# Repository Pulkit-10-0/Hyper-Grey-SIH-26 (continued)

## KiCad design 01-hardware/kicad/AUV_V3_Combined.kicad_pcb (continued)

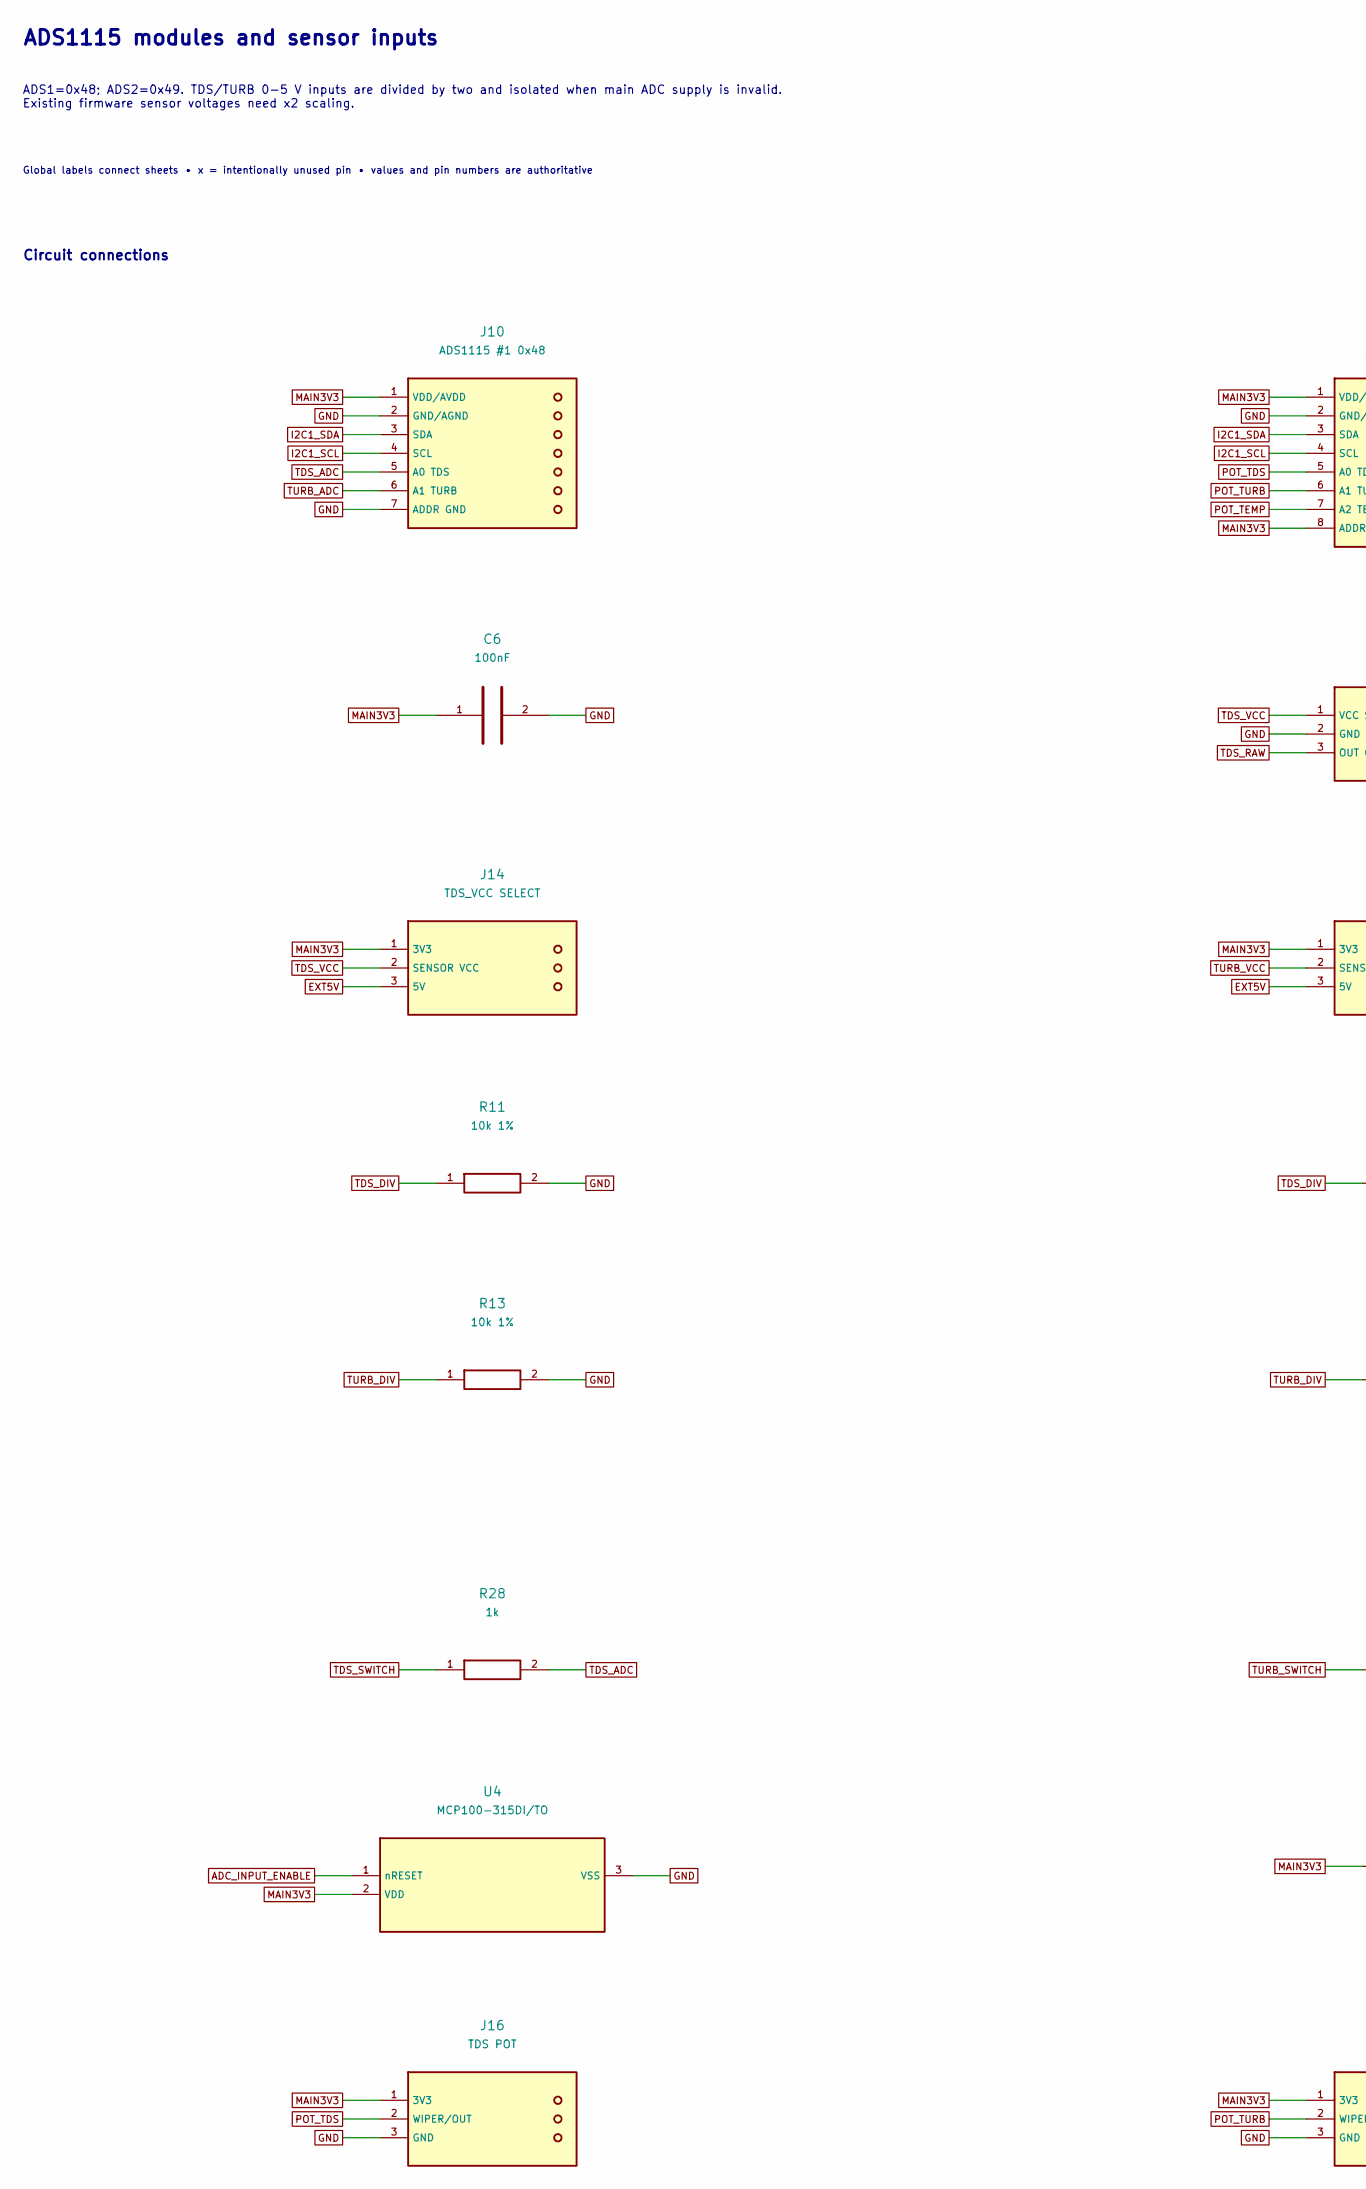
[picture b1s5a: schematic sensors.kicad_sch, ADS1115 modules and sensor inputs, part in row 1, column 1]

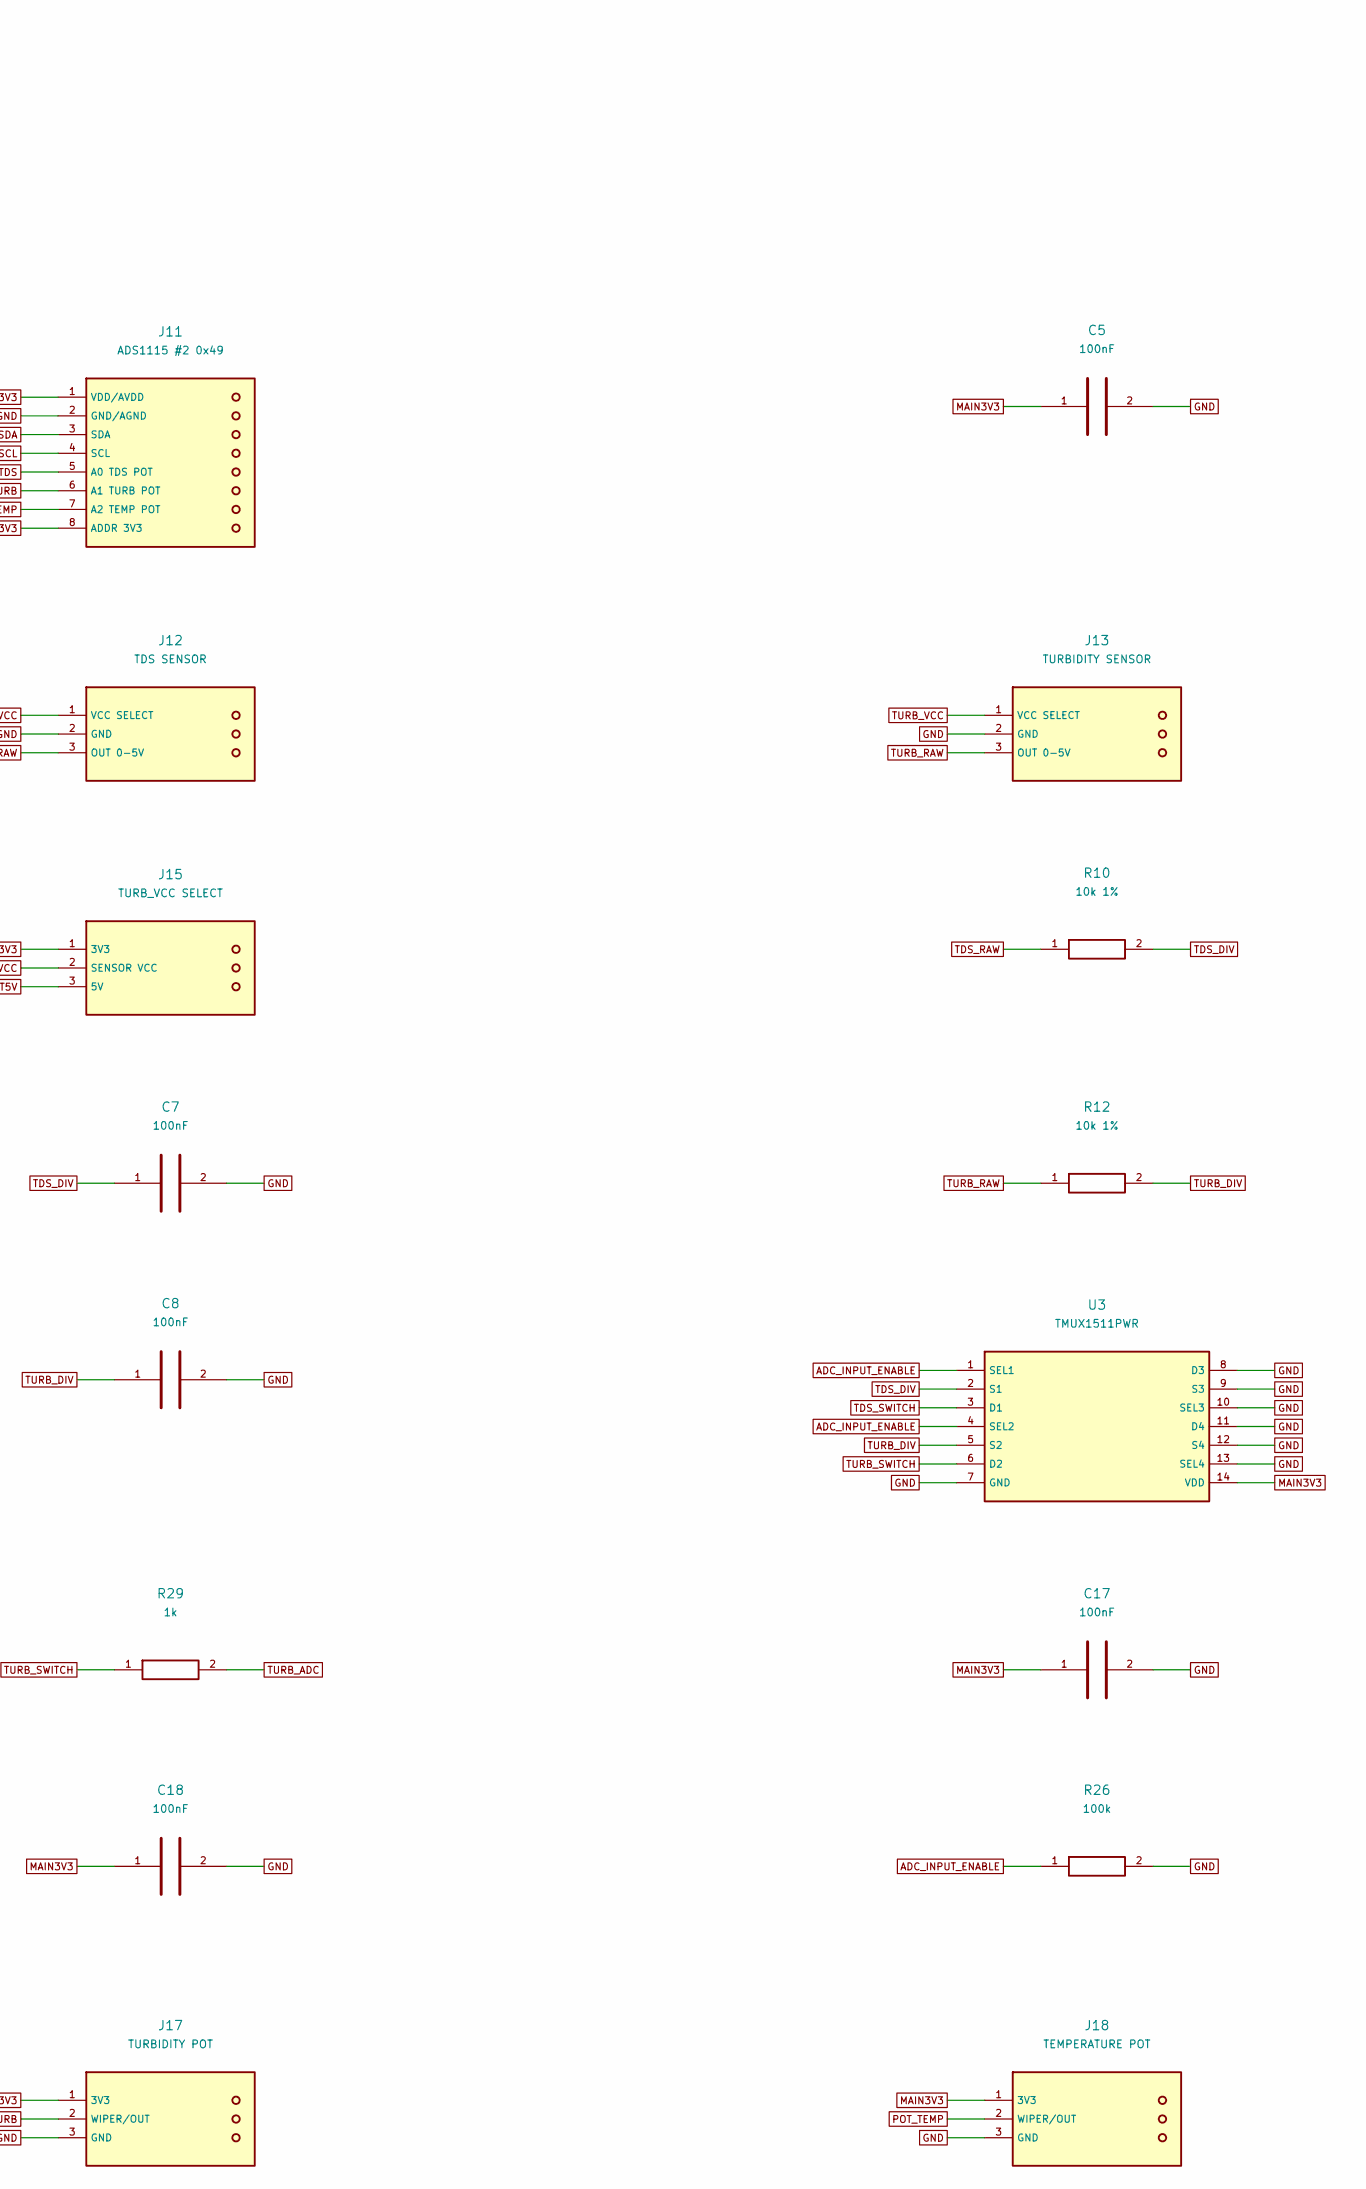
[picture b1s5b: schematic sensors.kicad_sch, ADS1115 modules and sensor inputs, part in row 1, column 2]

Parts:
C5, C6, C7, C8, C17, C18: 100nF; C_Disc_D3.0mm_W1.6mm_P2.50mm
J10: ADS1115 #1 0x48; WirePads_1x07; MPN Bare plated through-hole wiring pads
J11: ADS1115 #2 0x49; WirePads_1x08; MPN Bare plated through-hole wiring pads
J12: TDS SENSOR; WirePads_1x03; MPN Bare plated through-hole wiring pads
J13: TURBIDITY SENSOR; WirePads_1x03; MPN Bare plated through-hole wiring pads
J14: TDS_VCC SELECT; PinHeader_1x03_P2.54mm_Vertical
J15: TURB_VCC SELECT; PinHeader_1x03_P2.54mm_Vertical
J16: TDS POT; WirePads_1x03; MPN Bare plated through-hole wiring pads
J17: TURBIDITY POT; WirePads_1x03; MPN Bare plated through-hole wiring pads
J18: TEMPERATURE POT; WirePads_1x03; MPN Bare plated through-hole wiring pads
R10, R11, R12, R13: 10k 1%; R_Axial_DIN0207_L6.3mm_D2.5mm_P7.62mm_Horizontal
R26: 100k; R_Axial_DIN0207_L6.3mm_D2.5mm_P7.62mm_Horizontal
R28, R29: 1k; R_Axial_DIN0207_L6.3mm_D2.5mm_P7.62mm_Horizontal
U3: TMUX1511PWR; TSSOP-14_4.4x5mm_P0.65mm; MPN TMUX1511PWR
U4: MCP100-315DI/TO; TO-92_Inline_Wide; MPN MCP100-315DI/TO

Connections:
ADC_INPUT_ENABLE: R26.1, U3.1 (SEL1), U3.4 (SEL2), U4.1 (nRESET)
EXT5V: J14.3 (5V), J15.3 (5V); also elsewhere on the board
GND: C5.2, C6.2, C7.2, C8.2, C17.2, C18.2, J10.2 (GND/AGND), J10.7 (ADDR GND), J11.2 (GND/AGND), J12.2 (GND), J13.2 (GND), J16.3 (GND), J17.3 (GND), J18.3 (GND), R11.2, R13.2, R26.2, U3.7 (GND), U3.8 (D3), U3.9 (S3), U3.10 (SEL3), U3.11 (D4), U3.12 (S4), U3.13 (SEL4), U4.3 (VSS); also elsewhere on the board
I2C1_SCL: J10.4 (SCL), J11.4 (SCL); also elsewhere on the board
I2C1_SDA: J10.3 (SDA), J11.3 (SDA); also elsewhere on the board
MAIN3V3: C5.1, C6.1, C17.1, C18.1, J10.1 (VDD/AVDD), J11.1 (VDD/AVDD), J11.8 (ADDR 3V3), J14.1 (3V3), J15.1 (3V3), J16.1 (3V3), J17.1 (3V3), J18.1 (3V3), U3.14 (VDD), U4.2 (VDD); also elsewhere on the board
POT_TDS: J11.5 (A0 TDS POT), J16.2 (WIPER/OUT)
POT_TEMP: J11.7 (A2 TEMP POT), J18.2 (WIPER/OUT)
POT_TURB: J11.6 (A1 TURB POT), J17.2 (WIPER/OUT)
TDS_ADC: J10.5 (A0 TDS), R28.2
TDS_DIV: C7.1, R10.2, R11.1, U3.2 (S1)
TDS_RAW: J12.3 (OUT 0-5V), R10.1
TDS_SWITCH: R28.1, U3.3 (D1)
TDS_VCC: J12.1 (VCC SELECT), J14.2 (SENSOR VCC)
TURB_ADC: J10.6 (A1 TURB), R29.2
TURB_DIV: C8.1, R12.2, R13.1, U3.5 (S2)
TURB_RAW: J13.3 (OUT 0-5V), R12.1
TURB_SWITCH: R29.1, U3.6 (D2)
TURB_VCC: J13.1 (VCC SELECT), J15.2 (SENSOR VCC)

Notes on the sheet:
ADS1115 modules and sensor inputs
ADS1=0x48; ADS2=0x49. TDS/TURB 0-5 V inputs are divided by two and isolated when main ADC supply is invalid. Existing firmware sensor voltages need x2 scaling.
Global labels connect sheets • x = intentionally unused pin • values and pin numbers are authoritative
Circuit connections

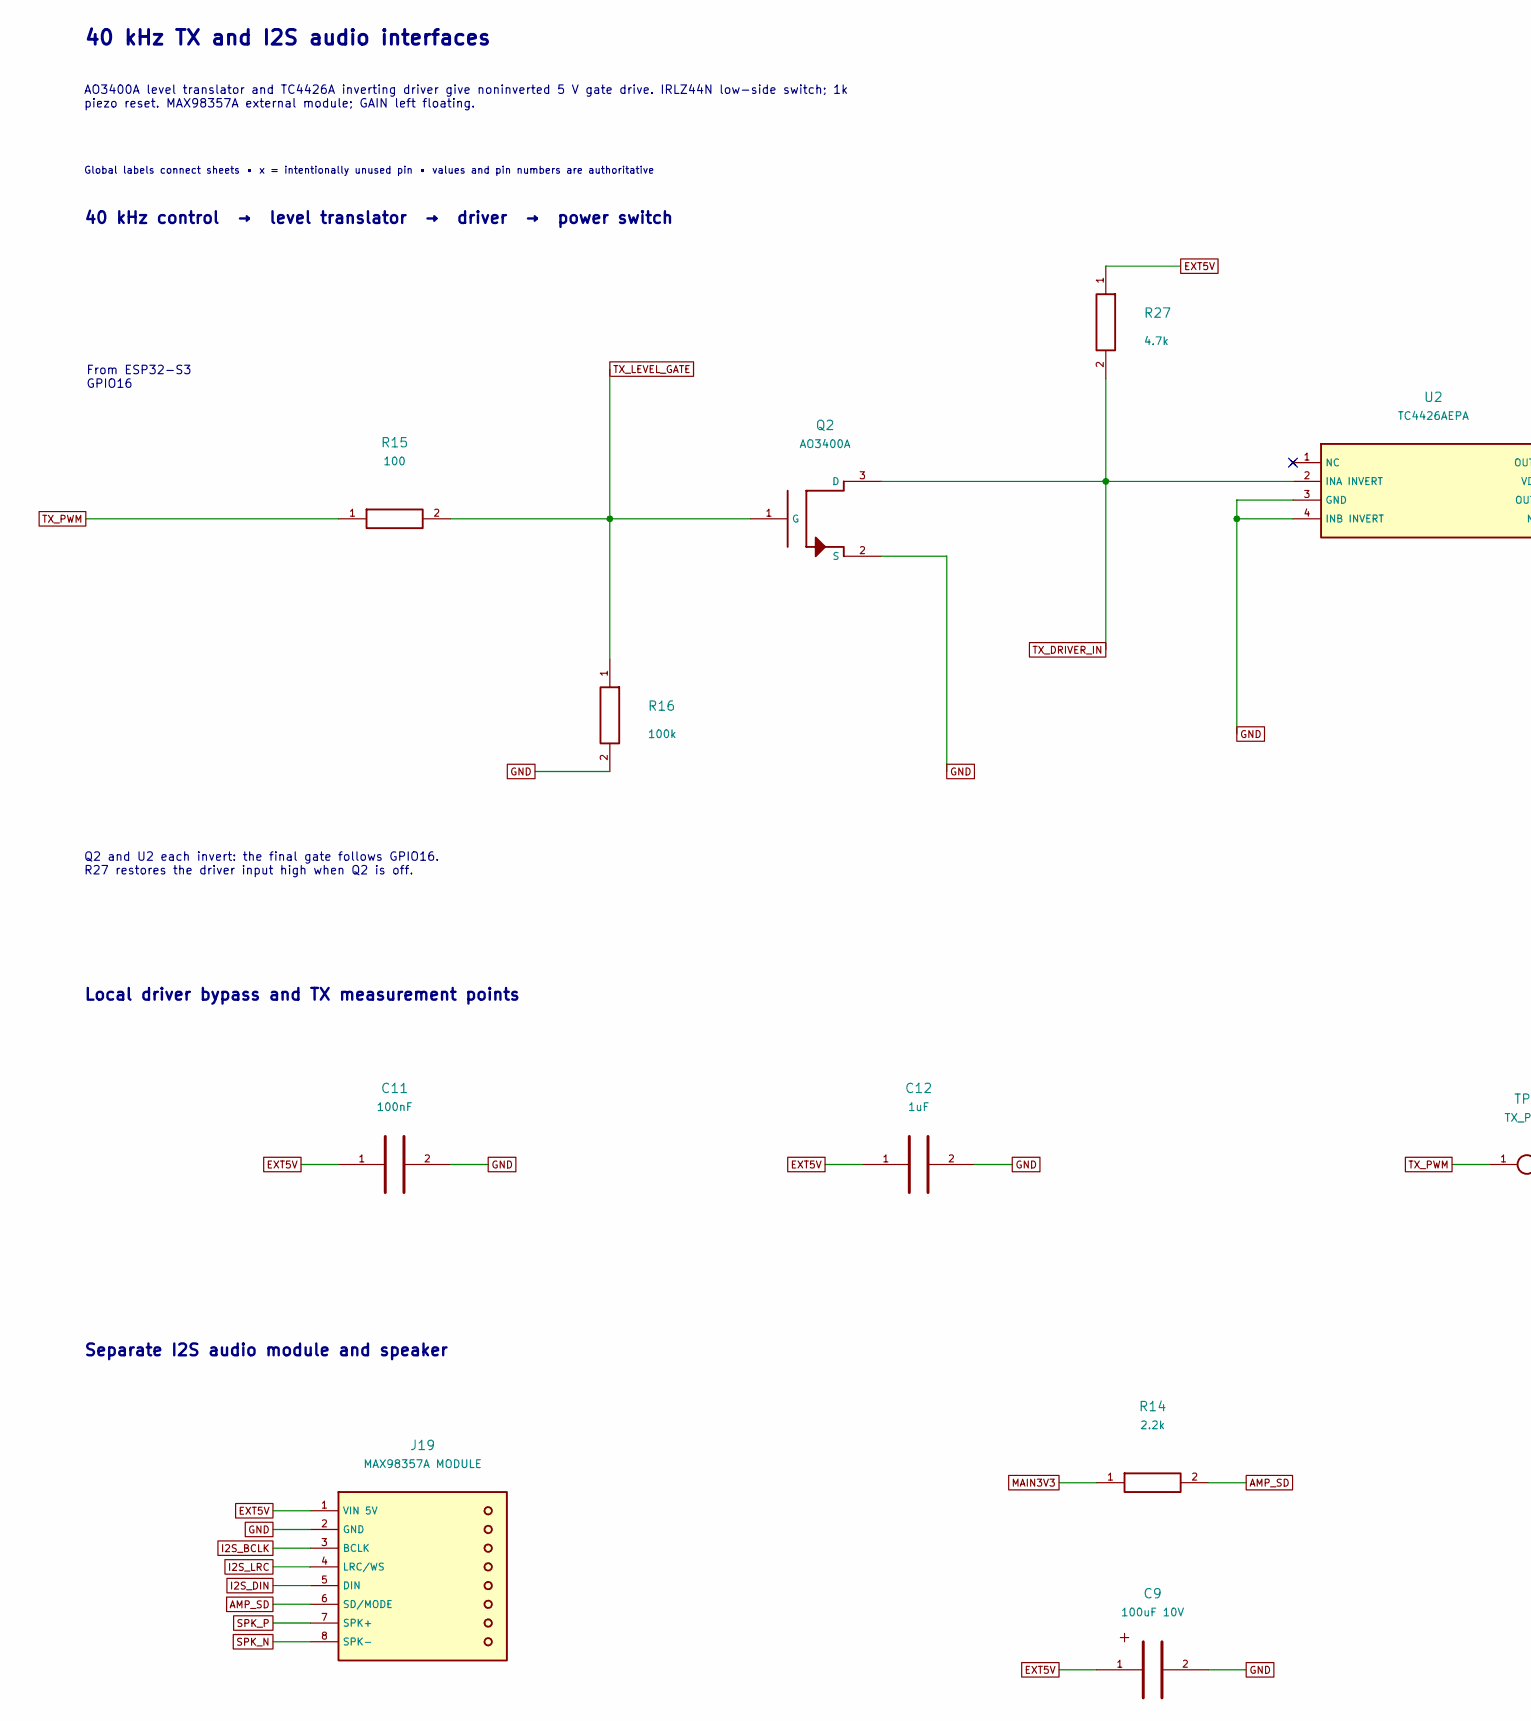
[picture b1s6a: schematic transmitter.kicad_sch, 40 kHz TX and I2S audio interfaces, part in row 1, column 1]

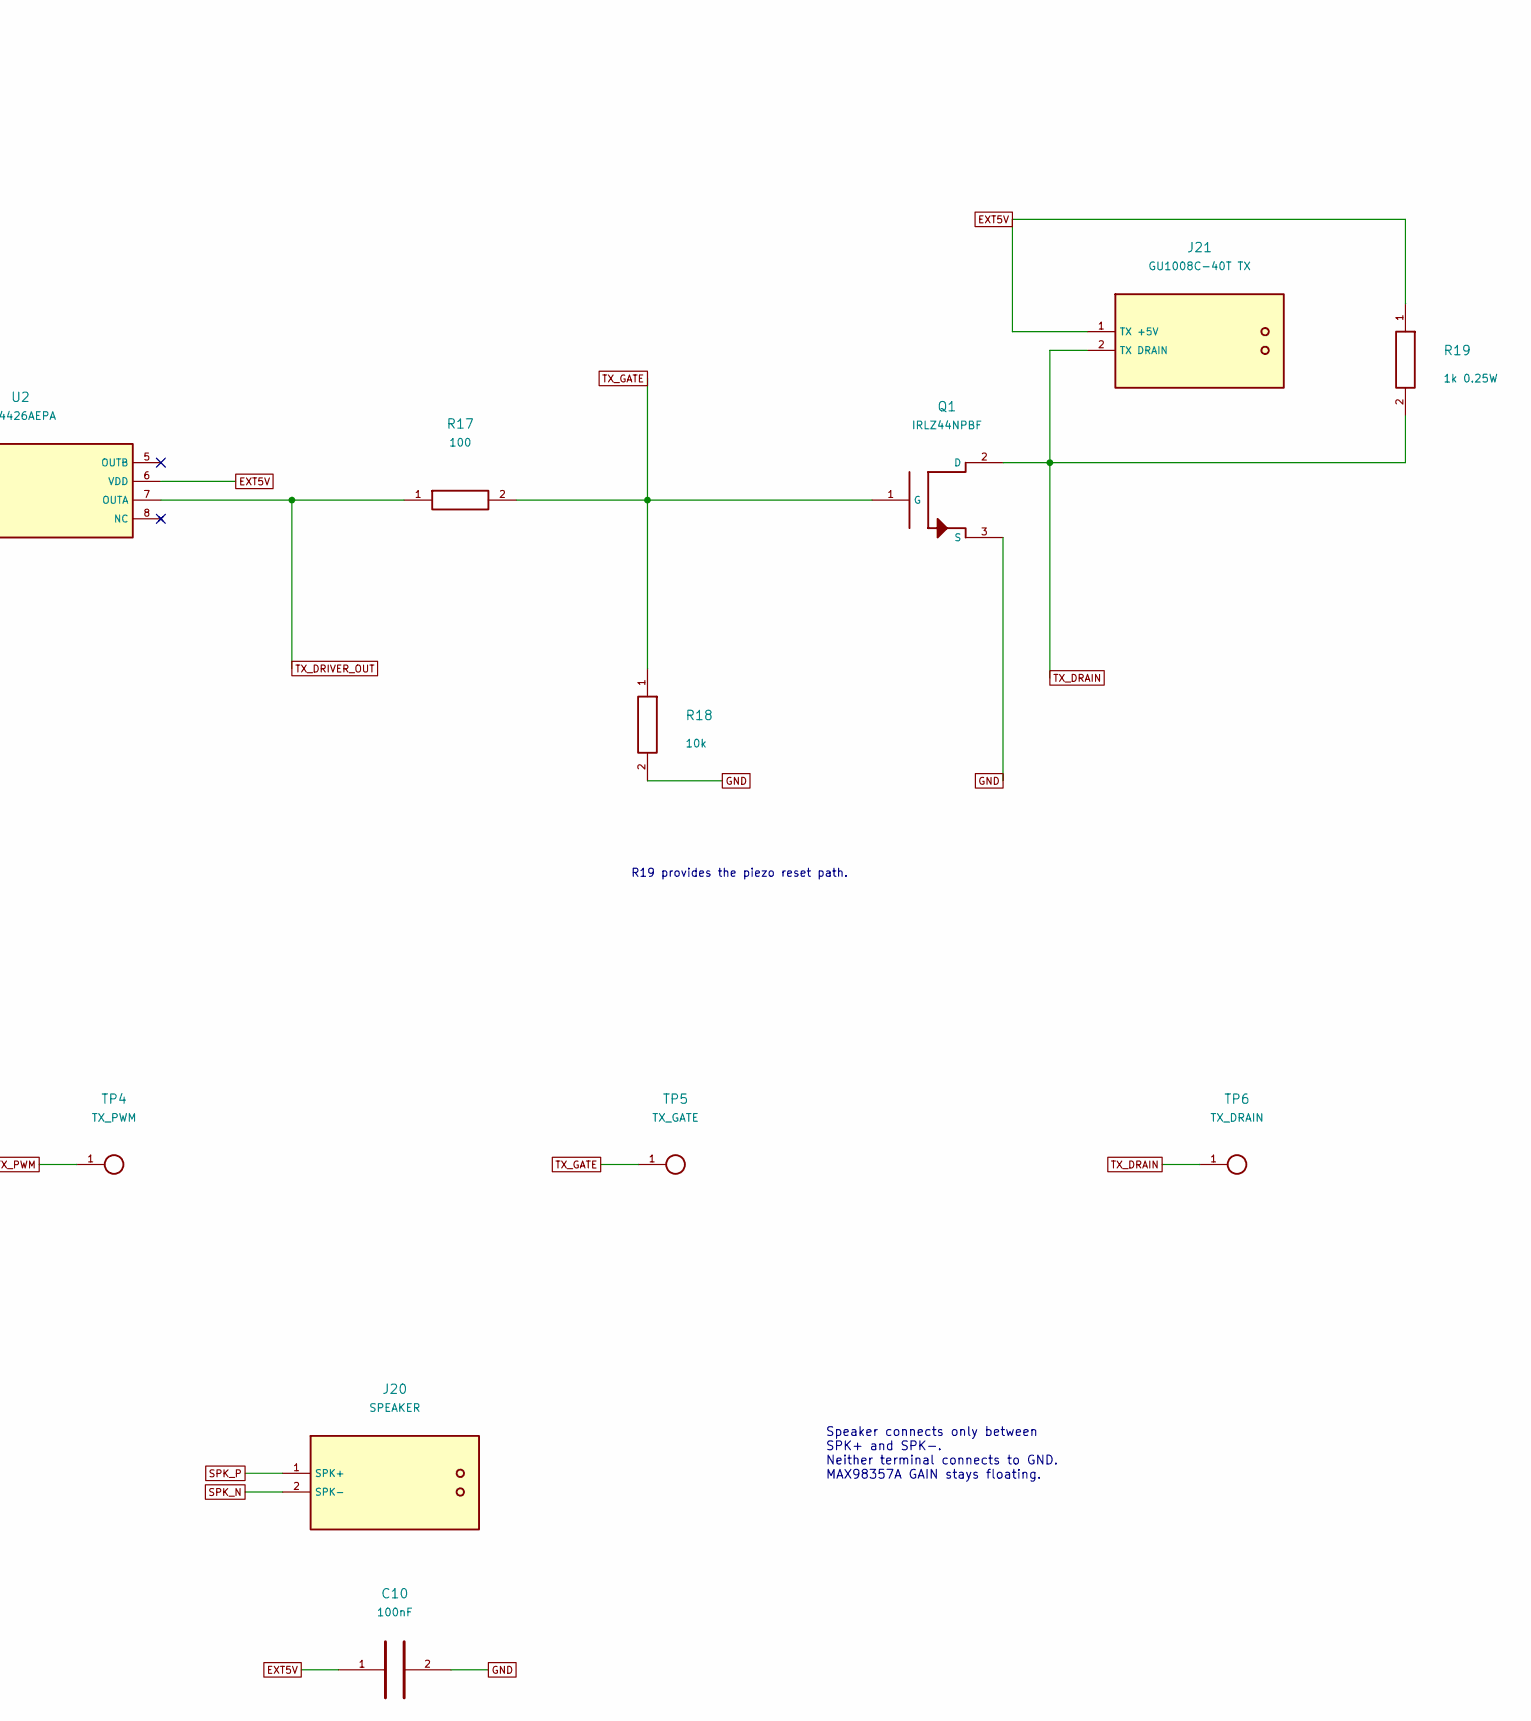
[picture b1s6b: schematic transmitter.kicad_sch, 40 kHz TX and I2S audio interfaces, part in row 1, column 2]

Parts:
C9: 100uF 10V; CP_Radial_D6.3mm_P2.50mm
C10, C11: 100nF; C_Disc_D3.0mm_W1.6mm_P2.50mm
C12: 1uF; C_Disc_D3.0mm_W1.6mm_P2.50mm
J19: MAX98357A MODULE; WirePads_1x08; MPN Bare plated through-hole wiring pads
J20: SPEAKER; WirePads_1x02; MPN Bare plated through-hole wiring pads
J21: GU1008C-40T TX; WirePads_1x02; MPN Bare plated through-hole wiring pads
Q1: IRLZ44NPBF; TO-220-3_Vertical; MPN IRLZ44NPBF
Q2: AO3400A; SOT-23; MPN AO3400A
R14: 2.2k; R_Axial_DIN0207_L6.3mm_D2.5mm_P7.62mm_Horizontal
R15, R17: 100; R_Axial_DIN0207_L6.3mm_D2.5mm_P7.62mm_Horizontal
R16: 100k; R_Axial_DIN0207_L6.3mm_D2.5mm_P7.62mm_Horizontal
R18: 10k; R_Axial_DIN0207_L6.3mm_D2.5mm_P7.62mm_Horizontal
R19: 1k 0.25W; R_Axial_DIN0207_L6.3mm_D2.5mm_P7.62mm_Horizontal
R27: 4.7k; R_Axial_DIN0207_L6.3mm_D2.5mm_P7.62mm_Horizontal
TP4: TX_PWM; TestPoint_THTPad_D2.0mm_Drill1.0mm
TP5: TX_GATE; TestPoint_THTPad_D2.0mm_Drill1.0mm
TP6: TX_DRAIN; TestPoint_THTPad_D2.0mm_Drill1.0mm
U2: TC4426AEPA; DIP-8_W7.62mm_Socket_LongPads; MPN TC4426AEPA

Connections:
AMP_SD: J19.6 (SD/MODE), R14.2
EXT5V: C9.1, C10.1, C11.1, C12.1, J19.1 (VIN 5V), J21.1 (TX +5V), R19.1, R27.1, U2.6 (VDD); also elsewhere on the board
GND: C9.2, C10.2, C11.2, C12.2, J19.2 (GND), Q1.3 (S), Q2.2 (S), R16.2, R18.2, U2.3 (GND), U2.4 (INB INVERT); also elsewhere on the board
I2S_BCLK: J19.3 (BCLK); also elsewhere on the board
I2S_DIN: J19.5 (DIN); also elsewhere on the board
I2S_LRC: J19.4 (LRC/WS); also elsewhere on the board
MAIN3V3: R14.1; also elsewhere on the board
SPK_N: J19.8 (SPK-), J20.2 (SPK-)
SPK_P: J19.7 (SPK+), J20.1 (SPK+)
TX_DRAIN: J21.2 (TX DRAIN), Q1.2 (D), R19.2, TP6.1
TX_DRIVER_IN: Q2.3 (D), R27.2, U2.2 (INA INVERT)
TX_DRIVER_OUT: R17.1, U2.7 (OUTA)
TX_GATE: Q1.1 (G), R17.2, R18.1, TP5.1
TX_LEVEL_GATE: Q2.1 (G), R15.2, R16.1
TX_PWM: R15.1, TP4.1; also elsewhere on the board

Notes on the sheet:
40 kHz TX and I2S audio interfaces
AO3400A level translator and TC4426A inverting driver give noninverted 5 V gate drive. IRLZ44N low-side switch; 1k piezo reset. MAX98357A external module; GAIN left floating.
Global labels connect sheets • x = intentionally unused pin • values and pin numbers are authoritative
40 kHz control → level translator → driver → power switch
From ESP32-S3 GPIO16
Q2 and U2 each invert: the final gate follows GPIO16. R27 restores the driver input high when Q2 is off.
R19 provides the piezo reset path.
Local driver bypass and TX measurement points
Separate I2S audio module and speaker
Speaker connects only between SPK+ and SPK-. Neither terminal connects to GND. MAX98357A GAIN stays floating.

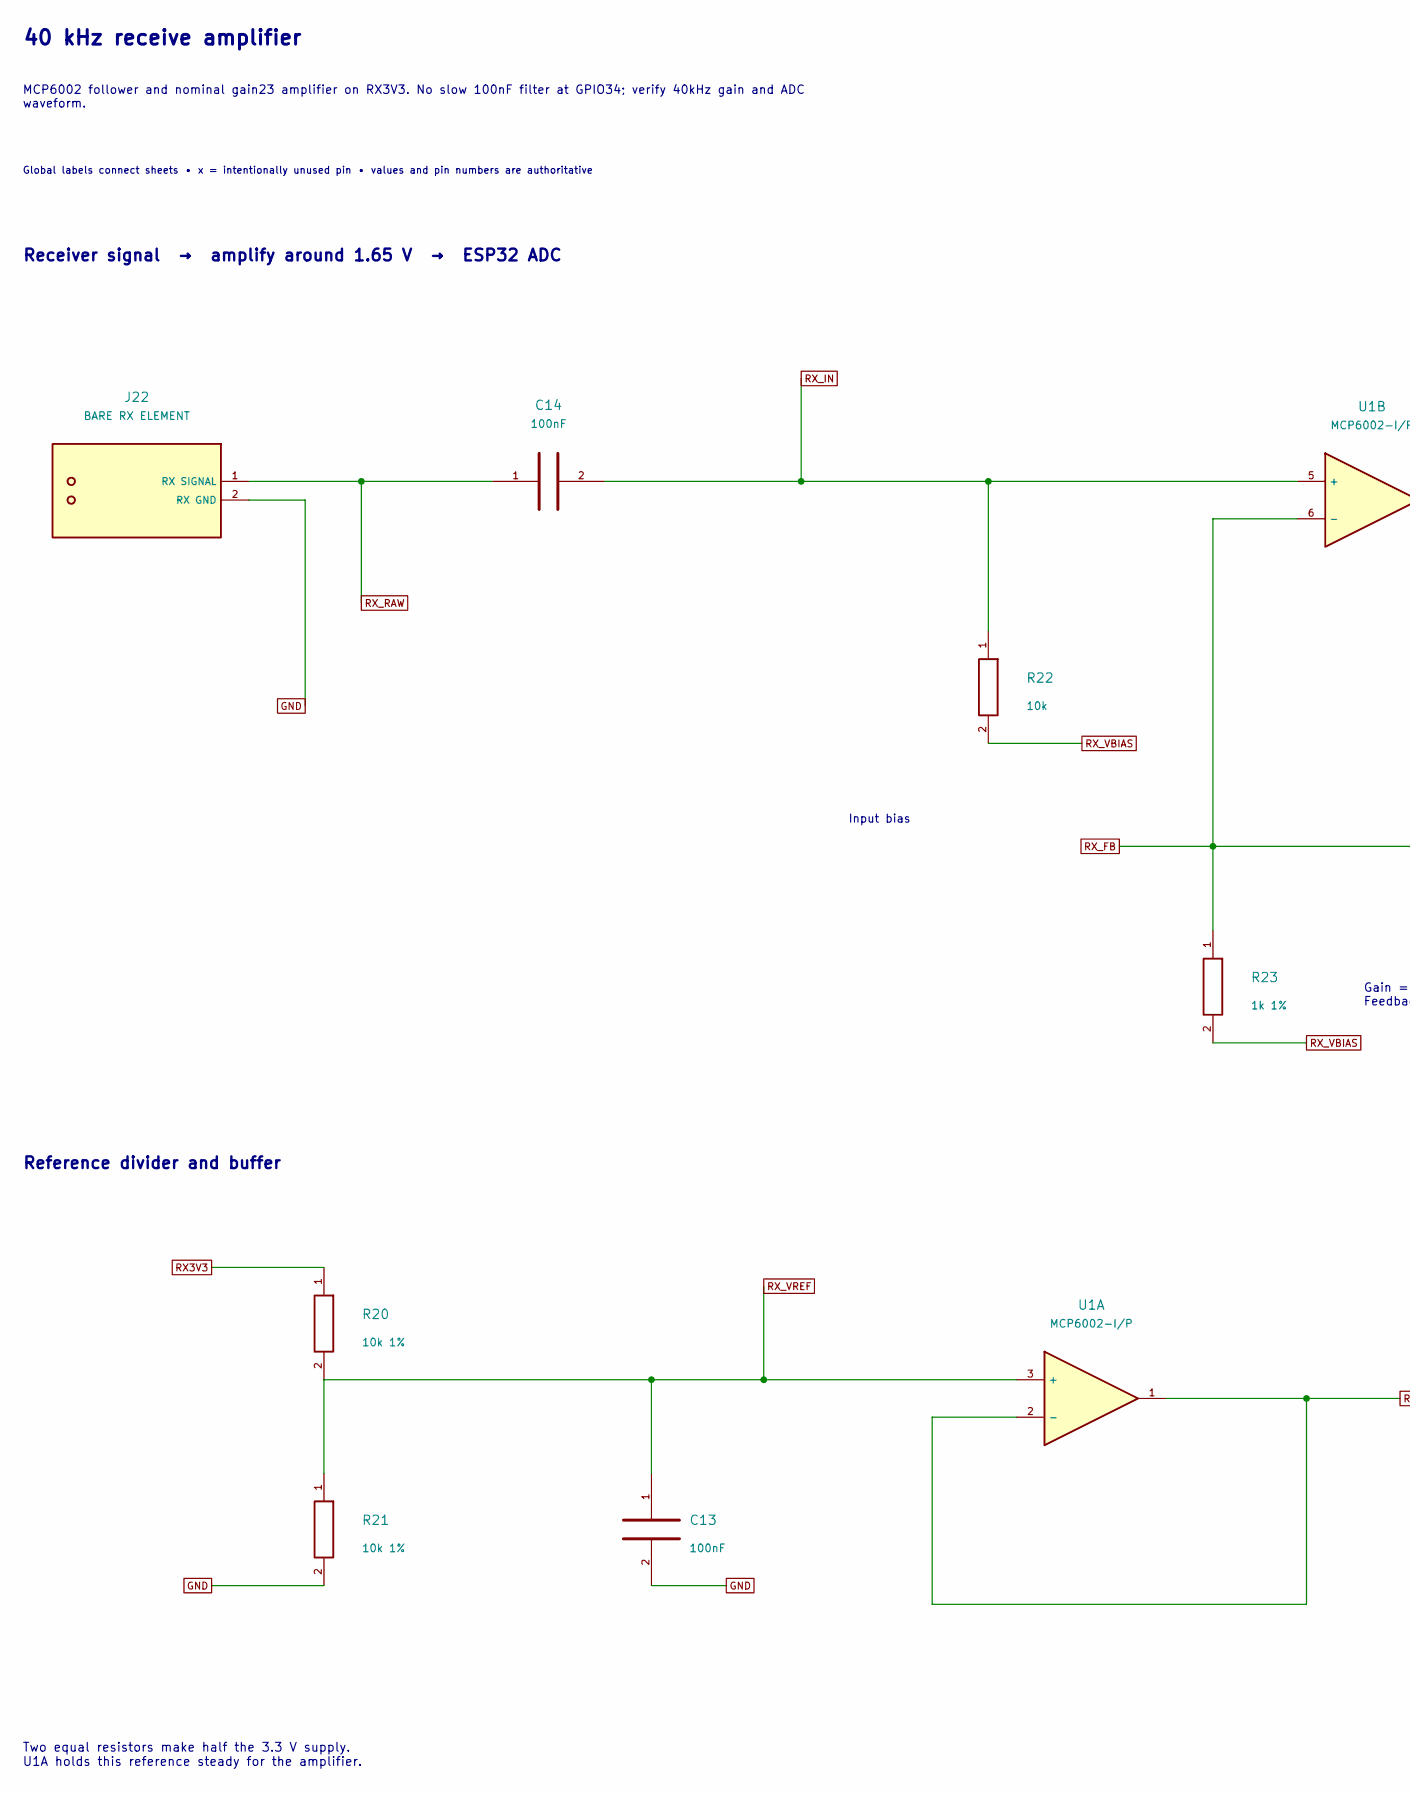
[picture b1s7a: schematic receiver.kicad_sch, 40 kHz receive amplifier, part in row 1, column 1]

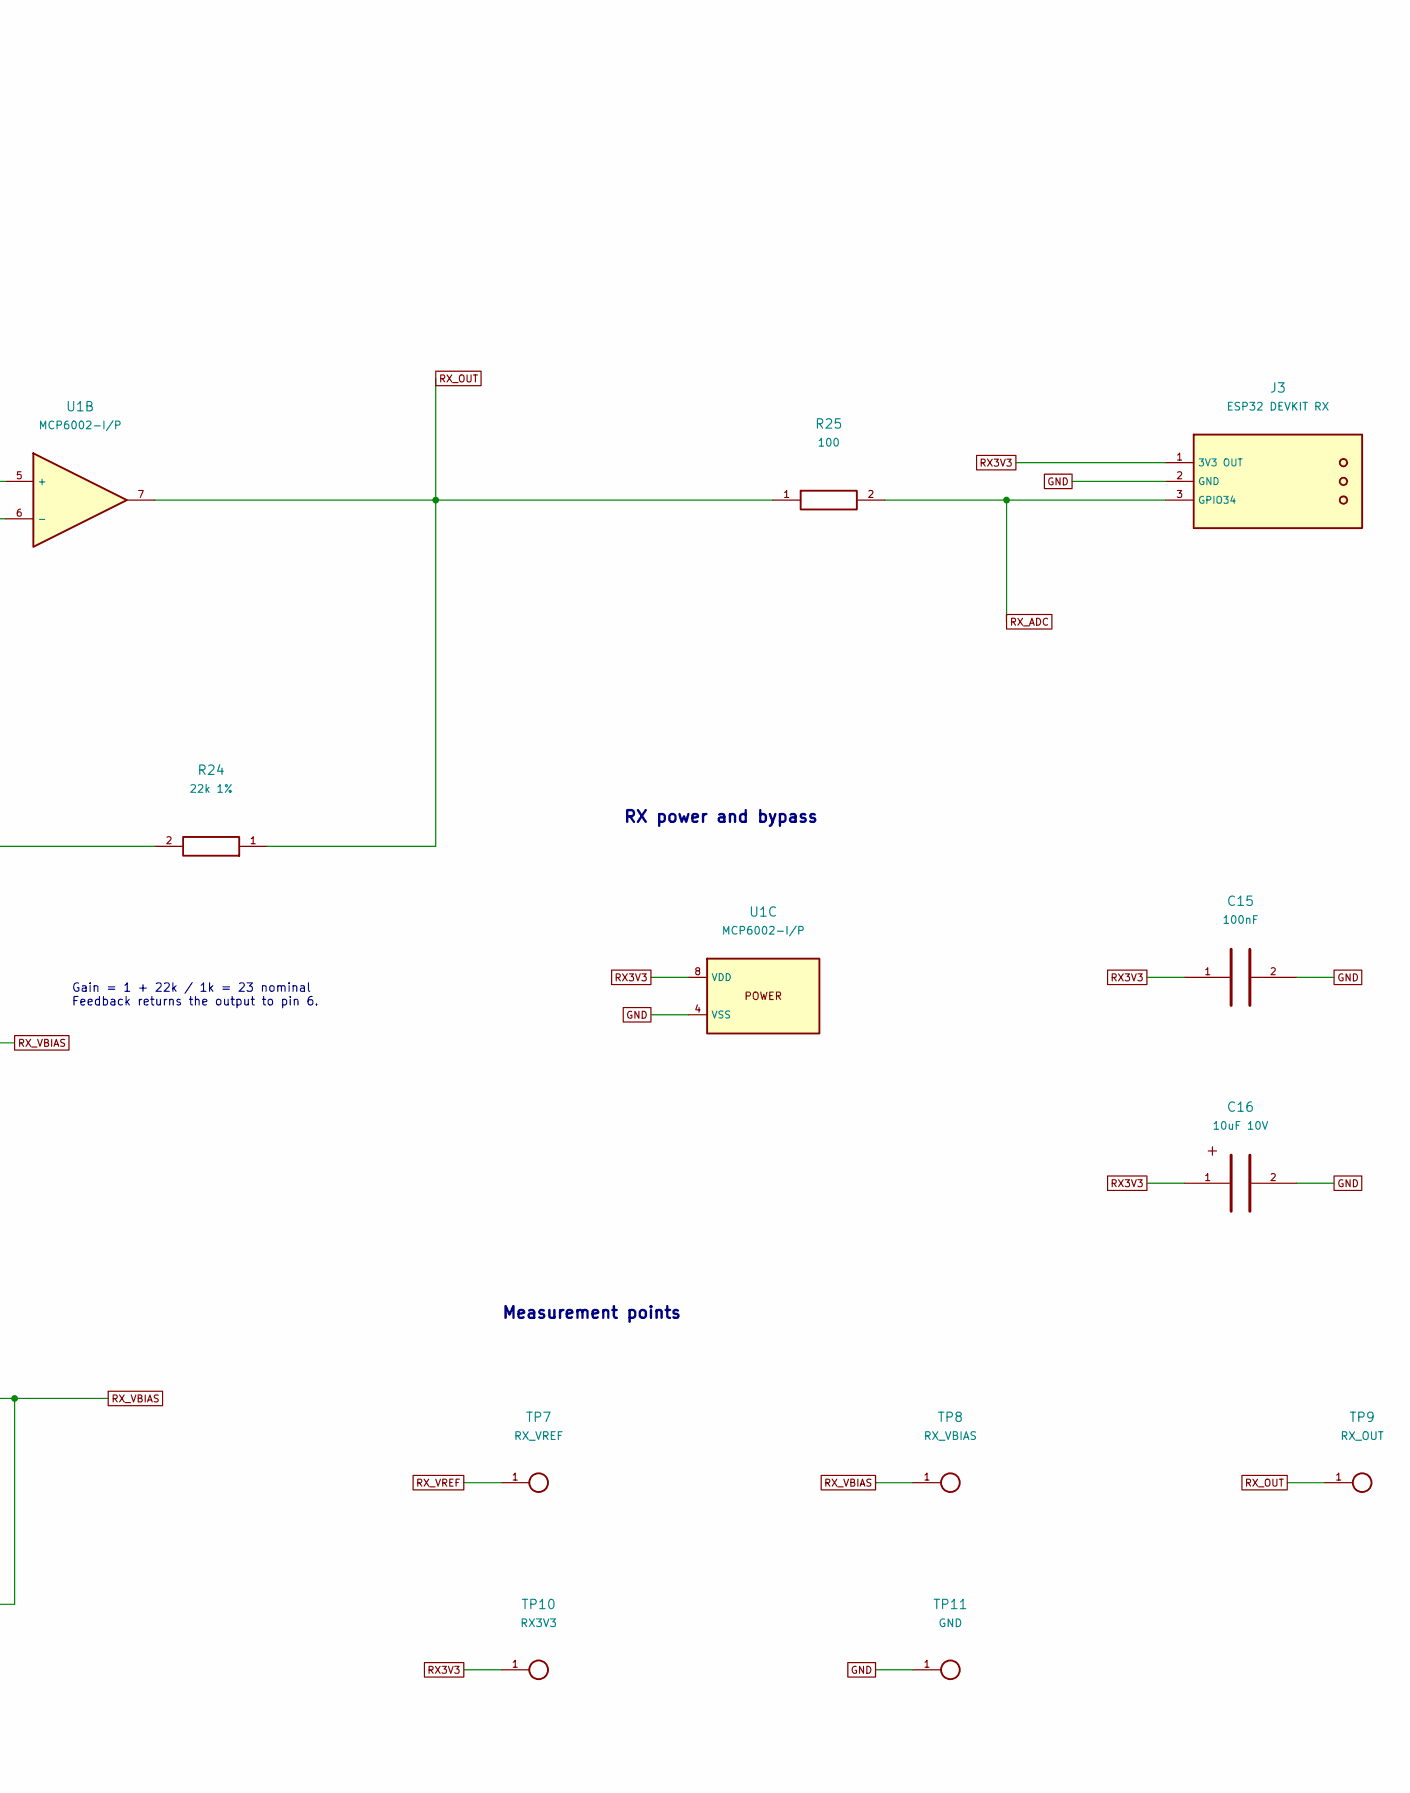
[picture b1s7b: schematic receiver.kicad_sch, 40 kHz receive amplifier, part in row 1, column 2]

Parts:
C13, C14, C15: 100nF; C_Disc_D3.0mm_W1.6mm_P2.50mm
C16: 10uF 10V; CP_Radial_D5.0mm_P2.00mm
J3: ESP32 DEVKIT RX; WirePads_1x03; MPN Bare plated through-hole wiring pads
J22: BARE RX ELEMENT; WirePads_1x02; MPN Bare plated through-hole wiring pads
R20, R21: 10k 1%; R_Axial_DIN0207_L6.3mm_D2.5mm_P7.62mm_Horizontal
R22: 10k; R_Axial_DIN0207_L6.3mm_D2.5mm_P7.62mm_Horizontal
R23: 1k 1%; R_Axial_DIN0207_L6.3mm_D2.5mm_P7.62mm_Horizontal
R24: 22k 1%; R_Axial_DIN0207_L6.3mm_D2.5mm_P7.62mm_Horizontal
R25: 100; R_Axial_DIN0207_L6.3mm_D2.5mm_P7.62mm_Horizontal
TP7: RX_VREF; TestPoint_THTPad_D2.0mm_Drill1.0mm
TP8: RX_VBIAS; TestPoint_THTPad_D2.0mm_Drill1.0mm
TP9: RX_OUT; TestPoint_THTPad_D2.0mm_Drill1.0mm
TP10: RX3V3; TestPoint_THTPad_D2.0mm_Drill1.0mm
TP11: GND; TestPoint_THTPad_D2.0mm_Drill1.0mm
U1: MCP6002-I/P; DIP-8_W7.62mm_Socket_LongPads; MPN MCP6002-I/P

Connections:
GND: C13.2, C15.2, C16.2, J3.2 (GND), J22.2 (RX GND), R21.2, TP11.1, U1.4 (VSS); also elsewhere on the board
RX3V3: C15.1, C16.1, J3.1 (3V3 OUT), R20.1, TP10.1, U1.8 (VDD)
RX_ADC: J3.3 (GPIO34), R25.2
RX_FB: R23.1, R24.2, U1.6 (−)
RX_IN: C14.2, R22.1, U1.5 (+)
RX_OUT: R24.1, R25.1, TP9.1, U1.7
RX_RAW: C14.1, J22.1 (RX SIGNAL)
RX_VBIAS: R22.2, R23.2, TP8.1, U1.1, U1.2 (−)
RX_VREF: C13.1, R20.2, R21.1, TP7.1, U1.3 (+)

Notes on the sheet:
40 kHz receive amplifier
MCP6002 follower and nominal gain23 amplifier on RX3V3. No slow 100nF filter at GPIO34; verify 40kHz gain and ADC waveform.
Global labels connect sheets • x = intentionally unused pin • values and pin numbers are authoritative
Receiver signal → amplify around 1.65 V → ESP32 ADC
Input bias
Gain = 1 + 22k / 1k = 23 nominal Feedback returns the output to pin 6.
Reference divider and buffer
Two equal resistors make half the 3.3 V supply. U1A holds this reference steady for the amplifier.
RX power and bypass
Measurement points
